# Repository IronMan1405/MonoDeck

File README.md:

# MonoDeck v2

A compact, handheld game console built around the Raspberry Pi Pico 2 W, featuring a 128×64 OLED display and a custom game engine with a registry-based architecture.

---

## Games

| Game | Description |
|------|-------------|
| Snake | Classic snake |
| Pong | One-paddle pong |
| Breakout | Block-breaking arcade game |
| Tetricore | Tetris-style falling block game |
| Flappy | Flappy bird style arcade runner game |
| Conway's Game of Life | A zero Player game (find out if you don't know ) |
| Mines | Minesweeper |
---

## Hardware

### Bill of Materials

| Component | Details |
|-----------|---------|
| Microcontroller | Raspberry Pi Pico 2 W |
| Display | SH110x 128×64 OLED (I2C) |
| PCB | Custom PCB |
| Prototyping | Breadboard |
| Enclosure | 3D printed case |
| Power | Li-Po battery |

### Wiring

The display communicates over I2C. Default pin configuration is defined in `platform/platform_config.h`.
| Component Pin | Pico GPIO | 
|---------------|-----------|
| OLED SDA | GPIO 8 |
| OLED SCL | GPIO 9 |
| Up Button | GPIO 11 |
| Down Button | GPIO 12 |
| Left Button | GPIO 13 |
| Right Button | GPIO 10 |
| A Button | GPIO 20 |
| B Button | GPIO 21 |
| SEL Button | GPIO 3 |
| START Button | GPIO 2 |

---

## Project Structure

```
MonoDeck_v2/
├── MonoDeck_v2.c          # Entry point / main loop
├── app_registry/
│   ├── app_registry.h     # Game struct definition, extern declarations
│   └── app_registry.c     # Game registry table — only file to edit when adding a game
├── core/
│   ├── app_state.h/.c     # AppState enum (BOOT, MENU, IN_GAME)
│   ├── engine.h/.c        # launchGame, tickGame, requestExitToMenu
│   ├── input.h/.c         # Button input handling
│   └── boot.h/.c          # Boot sequence
├── menu/
│   └── menu.h/.c          # Scrollable game menu
├── games/
│   ├── snake/
│   ├── pong/
│   ├── breakout/
│   └── tetricore/
├── drivers/
│   ├── sh110x/            # OLED display driver
│   └── buttons/           # button interface
├── platform/
│   ├── platform_config.h  # Pin definitions, I2C config
│   ├── platform_init.h/.c # Hardware initialisation
│   └── platform_time.h/.c # Timing utilities
├── hardware/
│   ├── pcb/
│   │   └── monodeck/
│   │       ├── *.kicad_pro
│   │       ├── *.kicad_sch
│   │       ├── *.kicad_pcb
│   │       └── (other KiCad files)
│   └── cad/
└── assets/                # Bitmaps, fonts
```

---

## Build Instructions

### Prerequisites

- [Raspberry Pi Pico SDK v2.2.0](https://github.com/raspberrypi/pico-sdk)
- CMake ≥ 3.13
- ARM GCC toolchain `14_2_Rel1` (`arm-none-eabi-gcc`)
- [picotool v2.2.0](https://github.com/raspberrypi/picotool)

The easiest way to get all of these is via the [Raspberry Pi Pico VS Code Extension](https://marketplace.visualstudio.com/items?itemName=raspberry-pi.raspberry-pi-pico), which installs the SDK, toolchain, and picotool automatically under `~/.pico-sdk/`.

### Build

```bash
git clone https://github.com/IronMan1405/MonoDeck_v2
cd MonoDeck_v2
mkdir build && cd build
cmake ..
make
```

This produces `MonoDeck_v2.uf2` in the `build/` directory.

> **Note:** The CMakeLists is configured for `pico2_w`. If you are using a standard Pico W, change `set(PICO_BOARD pico2_w ...)` to `set(PICO_BOARD pico_w ...)` before building.

### Flash

**Option A — VS Code (recommended)**
 
If you're using the Raspberry Pi Pico VS Code Extension:
 
1. Open the project in VS Code
2. Click the **Run** button in the Pico sidebar (or use `Ctrl+Shift+P` → `Raspberry Pi Pico: Run Project`)
3. The extension builds, flashes, and reboots the device automatically via picotool — no manual BOOTSEL needed
 
**Option B — Manual UF2**

1. Hold the **BOOTSEL** button on the Pico W and connect via USB
2. It mounts as a mass storage device
3. Copy `MonoDeck_v2.uf2` onto it — it will reboot automatically

---

## Adding a New Game

The registry architecture means adding a game requires changes to **one file only**.

### 1. Create your game files

```
games/
└── mygame/
    ├── mygame.h
    └── mygame.c
```

Your game must expose three functions:

```c
void initMyGame(void);
void updateMyGame(void);
void drawMyGame(void);
```

To exit back to the menu from within a game, call:

```c
#include "core/engine.h"

requestExitToMenu();
```

### 2. Register the game

Open `app_registry/app_registry.c` and add one `#include` and one entry:

```c
#include "games/mygame/mygame.h"   // add this

Game games[] = {
    {"Snake",     initSnake,     updateSnake,     drawSnake},
    {"Pong",      initPong,      updatePong,      drawPong},
    {"Breakout",  initBreakout,  updateBreakout,  drawBreakout},
    {"Tetricore", initTetricore, updateTetricore, drawTetricore},
    {"MyGame",    initMyGame,    updateMyGame,    drawMyGame},  // add this
};
```

### 3. Add highscore storage for the game

Open `platform/storage_map.h` and add the entry:

```c
typedef struct {
    uint32_t magic;
    uint16_t snake_hs;
    uint16_t pong_hs;
    uint16_t breakout_hs;
    uint16_t tetricore_hs;
    uint16_t mygame_hs;    // add this
    uint8_t  _pad[256 - 12];
} StoragePage;

// add this, make sure to keep the offset of the new game by 2 from the previous game
#define STORAGE_MYGAME_HIGHSCORE_OFFSET 0x008
```

Next open `platform/platform_storage.c` in the definition of ```loadStorage()``` add:

```c
void loadStorage(void) {
    ...

    if (page.magic == STORAGE_MAGIC) {
        gStorage = page;
    } else {
        gStorage.magic = STORAGE_MAGIC;
        gStorage.snake_hs = 0;
        gStorage.pong_hs = 0;
        gStorage.breakout_hs = 0;
        gStorage.tetricore_hs = 0;
        gStorage.mygame_hs = 0;     // add this
    }
}
```

And initialize it in your game's init function in `games/mygame/mygame.c`:

```c
#include "platform/platform_storage.h"

void initMyGame(void) {
    ...

    loadStorage();
    highScore = gStorage.mygame_hs;

    if (highScore < 0 || highScore > 999) highScore = 0;

    ...
}
```

*(Note: you can set the upper limit of highscore to anything, i have set it as 999 for most games, and 99999 for tetricore)*

---

## ToDo

- [x] Add Select & Start buttons interface
- [x] Add persistent high score storing
- [x] Refine Scoring methods
- [ ] Add levels & game modes
- [x] Add PCB files 
- [x] Add enclosure CAD files 
- [x] Implement Bi-directional rotation & wall kicks in Tetricore
- [x] UI/UX enhancements
- [x] Fix reverse scroll

---

## License

MIT

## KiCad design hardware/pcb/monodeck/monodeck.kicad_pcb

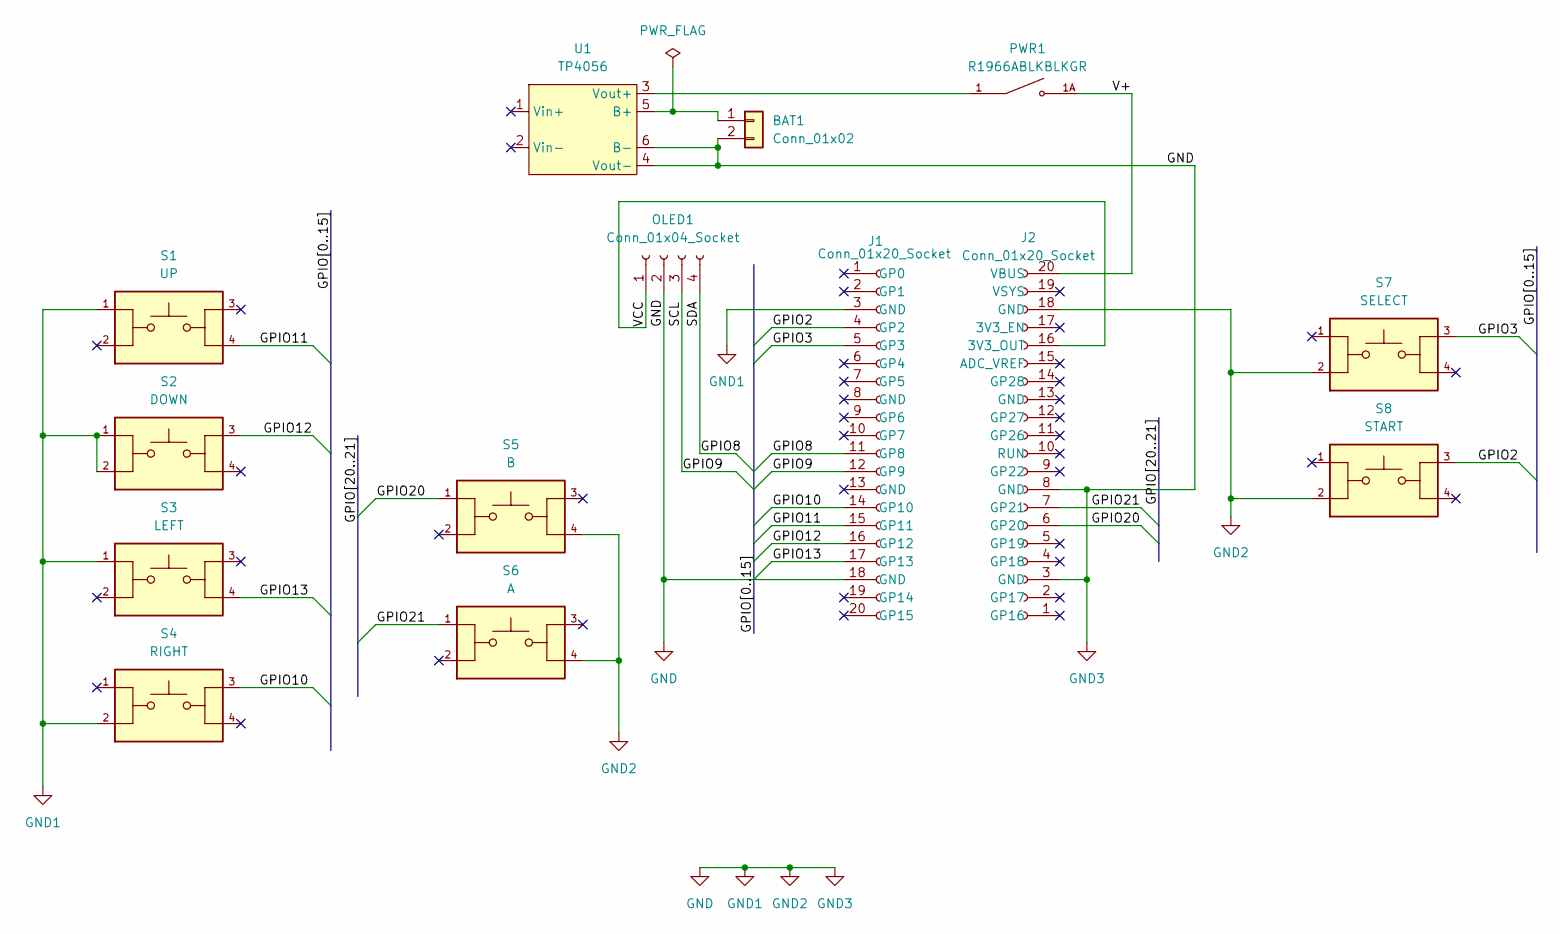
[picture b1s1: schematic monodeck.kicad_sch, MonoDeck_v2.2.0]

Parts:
BAT1: Conn_01x02; JST_PH_B2B-PH-K_1x02_P2.00mm_Vertical
J1, J2: Conn_01x20_Socket; PinSocket_1x20_P2.54mm_Vertical
OLED1: Conn_01x04_Socket; PinSocket_1x04_P2.54mm_Vertical
PWR1: R1966ABLKBLKGR; SW_R1966ABLKBLKGR; PARTREV E
S1: UP; SW_SWT0211-050010GSA_REVA; PARTREV A
S2: DOWN; SW_SWT0211-050010GSA_REVA; PARTREV A
S3: LEFT; SW_SWT0211-050010GSA_REVA; PARTREV A
S4: RIGHT; SW_SWT0211-050010GSA_REVA; PARTREV A
S5: B; SW_SWT0211-050010GSA_REVA; PARTREV A
S6: A; SW_SWT0211-050010GSA_REVA; PARTREV A
S7: SELECT; SW_SWT0211-050010GSA_REVA; PARTREV A
S8: START; SW_SWT0211-050010GSA_REVA; PARTREV A
U1: TP4056; TP4056-Module

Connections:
/GPIO2: J1.4 (GP2), S8.3
/GPIO3: J1.5 (GP3), S7.3
/GPIO8: J1.11 (GP8), OLED1.4
/GPIO9: J1.12 (GP9), OLED1.3
/GPIO10: J1.14 (GP10), S4.3
/GPIO11: J1.15 (GP11), S1.4
/GPIO12: J1.16 (GP12), S2.3
/GPIO13: J1.17 (GP13), S3.4
/GPIO20: J2.6 (GP20), S5.1
/GPIO21: J2.7 (GP21), S6.1
/V+: J2.20 (VBUS), PWR1.1A
/VCC: J2.16 (3V3_OUT), OLED1.1
GND: BAT1.2, J1.3 (GND), J1.18 (GND), J2.3 (GND), J2.8 (GND), J2.18 (GND), OLED1.2, S1.1, S2.1, S2.2, S3.1, S4.2, S5.4, S6.4, S7.2, S8.2, U1.4 (Vout-), U1.6 (B-)
unnamed: BAT1.1, U1.5 (B+)
unnamed: PWR1.1, U1.3 (Vout+)

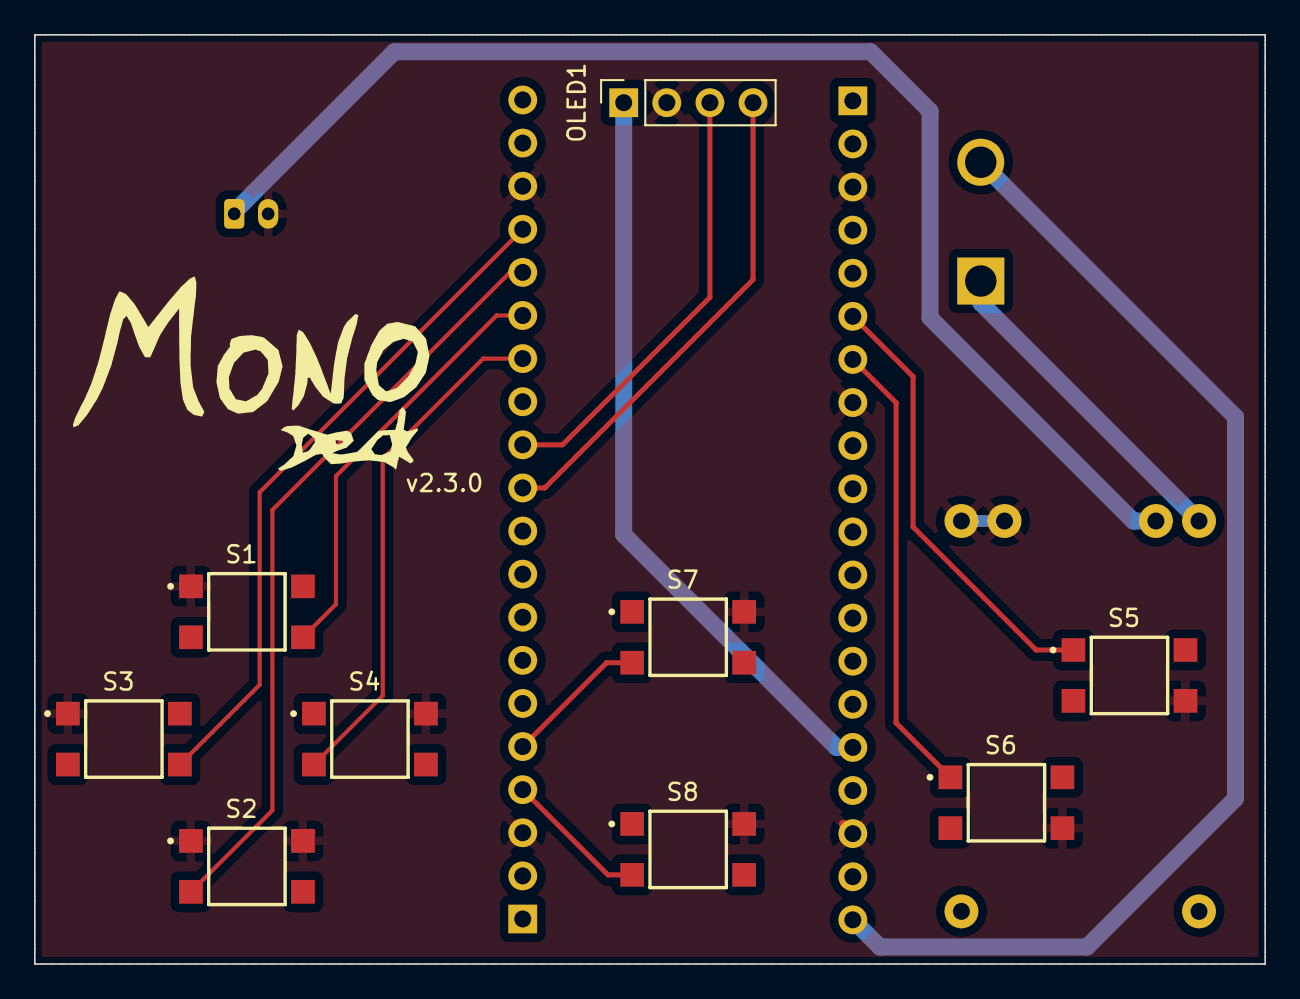
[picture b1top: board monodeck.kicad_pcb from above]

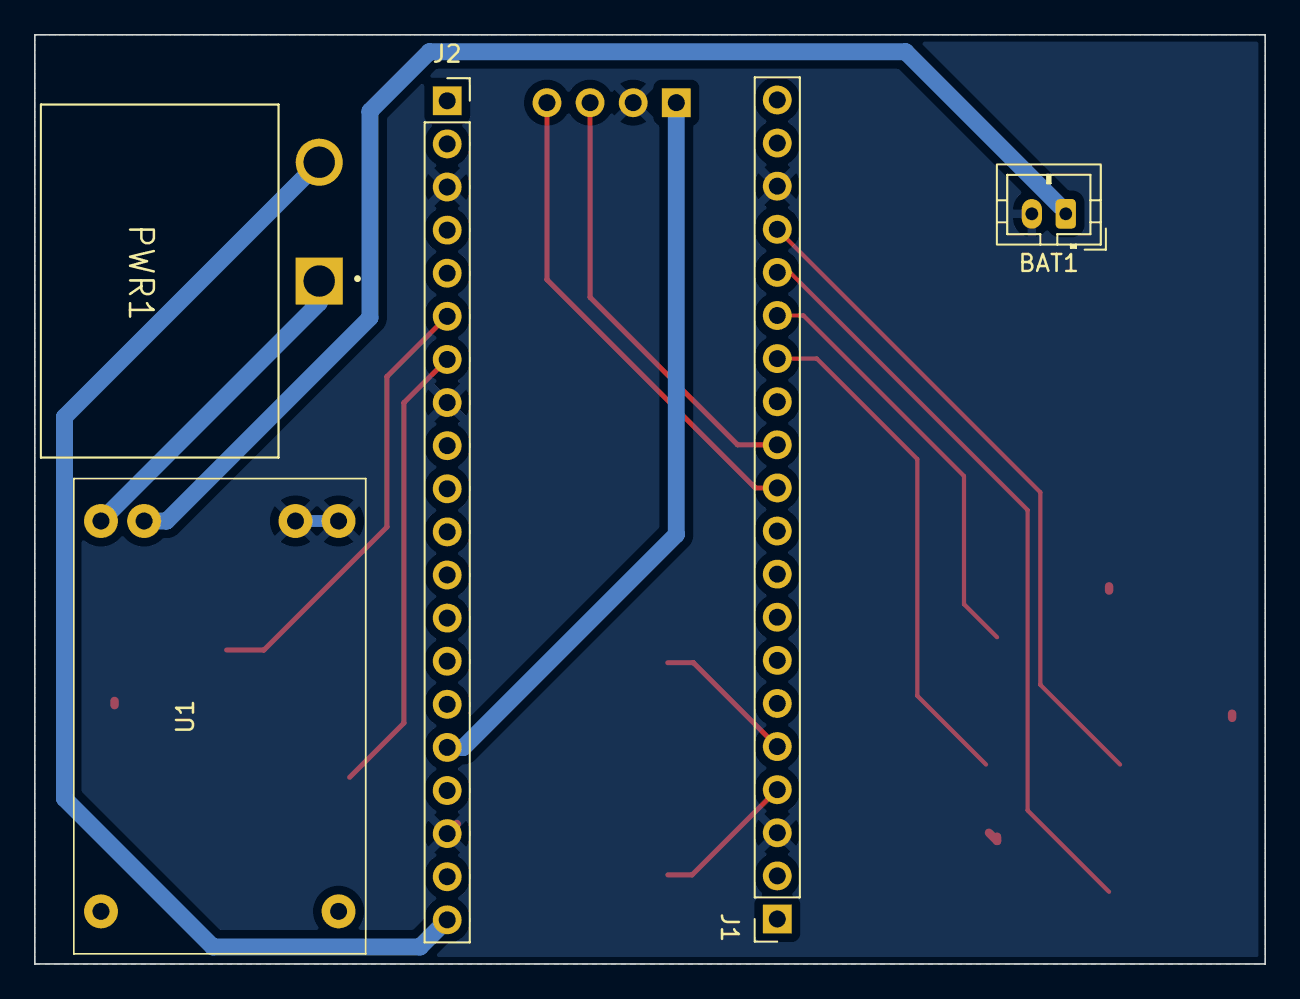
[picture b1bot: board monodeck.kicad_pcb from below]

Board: 2 copper layers, 72.5 x 54.8 mm, 14 parts (5 on the bottom side), 15 nets.

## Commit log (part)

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2025-12-15 Created Project Files
2025-12-15 updated gitignore
2025-12-15 Remove .vscode from repository
2025-12-15 Completed Menu & Title
2025-12-15 Finished Input logic
2025-12-16 Added Menu -> Game -> Menu Logic
2025-12-16 unify game state transitions via engine
2025-12-16 Added boot splash and Monodeck logo in menu
2025-12-16 added menu scroll
2025-12-18 Completed Snake v1
2025-12-19 Completed Pong (Single Player)
2025-12-19 Completed Breakout v1
2025-12-23 tetris basic done
2025-12-23 improvised tetricore
2026-01-21 Monodecl v1.0 — Arduino/PlatformIO final
2026-01-21 Monodecl v1.0 — ESP8266/PlatformIO final
2026-01-21 Initialize MonoDeck_v2 Pico
2026-01-21 Initialize Monodeck v2 Pico SDK project
2026-01-21 project folder structure set
2026-01-21 initialize and test pico
2026-02-15 completed oled driver
2026-02-18 wrote system and engine logic
2026-02-19 fixed button read, added monodeck logos
2026-02-23 added snake
2026-02-25 added pong
2026-02-25 added breakout
2026-02-25 added tetricore
2026-03-31 added app/game registry
2026-03-31 untracked .vscode
2026-03-31 fixed exit game bug
2026-03-31 fix: display edge warp bug, game exit bug
2026-03-31 untracked .DS_Store
2026-03-31 Add LICENSE file with MIT License
    Add MIT License file to the project.
2026-03-31 added README
2026-03-31 updated todo
2026-03-31 added persistent high score memory storage
2026-03-31 Update Pong description to one-paddle
2026-04-01 added select and start button interface in snake
2026-04-01 added select & start button interface
2026-04-01 updated TODO in Readme
2026-04-01 Fixed menu scroll
2026-04-02 implemented proper tetris scoring
2026-04-02 separated rotate and input delay, changed fall interval
2026-04-02 refined breakout physics, fixed highscore clamp for all games
2026-04-02 Update README with completed tasks
2026-04-03 finished schematic v1
2026-04-04 updated schematic
2026-04-05 made initial pcb, will edit it
2026-04-06 updated schematic and pcb, replaced pico smd with pin sockets
2026-04-06 added tp4056 module to the circuit
2026-04-06 finished first iteration of pcb
2026-04-08 added monodeck logo on pcb
2026-04-08 update: edited gnd plane to connect all gnd nets
2026-04-10 removed redundant traces
2026-04-10 updated pcb and dpad pin mapping for efficient routing
2026-04-10 generated drill and gerber files
2026-04-10 added BOM
2026-04-14 add PCB design for MonoDeck v2.2.0
2026-04-17 cad v1 done
2026-04-17 monoeck enclosure cad v2 done
2026-04-17 updated button pin maps & ToDo in README
2026-04-17 Enclosure cad v1.1 (#3)
    Cad for enclosure of monodeck is finalised for the upcoming version.
2026-04-18 added buttons cad (forgot last time)
2026-04-19 updated buttons cad, added deboss
2026-04-20 added flappy bird, updated seed logic for games that use rand()
2026-04-22 added conway's gol
2026-04-23 added minesweeper
2026-04-24 change screen window, bottom clearance inside case
2026-04-24 modified screen window and bottom internal clearance (#4)
2026-04-24 added clock (real)
